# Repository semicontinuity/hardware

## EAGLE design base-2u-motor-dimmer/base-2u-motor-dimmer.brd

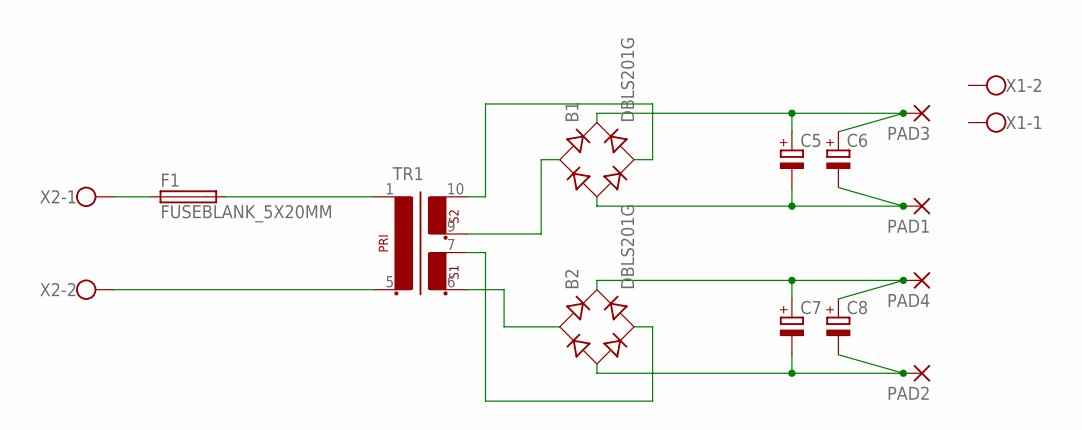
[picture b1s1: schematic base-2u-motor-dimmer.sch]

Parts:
B1, B2: DBLS201G; DBS
C5, C6, C7, C8: CPOL-EUTT2D5L; TT2D5L
F1: FUSEBLANK_5X20MM; FUSE_HOLDER_5X20MM
PAD1, PAD2, PAD3, PAD4: 1,6/0,8
TR1: EI30-2
X1, X2: W237-102

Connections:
unnamed: B2.AC2, TR1.7 (4)
unnamed: B2.AC1, TR1.6 (3)
unnamed: F1.1, X2.1
unnamed: B1.AC1, TR1.9 (5)
unnamed: B1.AC2, TR1.10 (6)
unnamed: B1.+, C5.+, C6.+, PAD3.1
unnamed: B1.-, C5.-, C6.-, PAD1.1
unnamed: B2.-, C7.-, C8.-, PAD2.1
unnamed: B2.+, C7.+, C8.+, PAD4.1

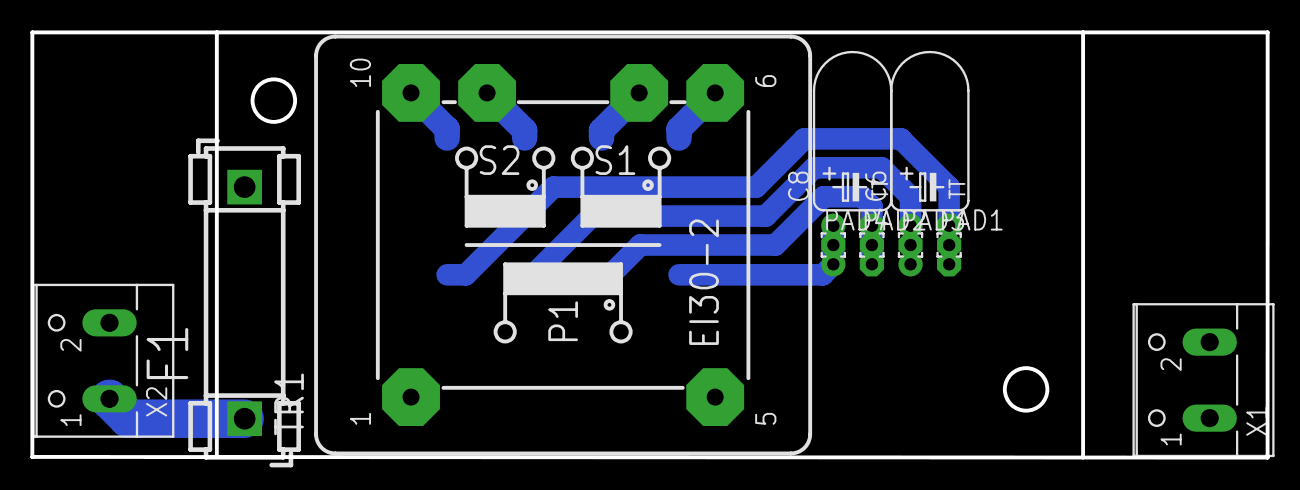
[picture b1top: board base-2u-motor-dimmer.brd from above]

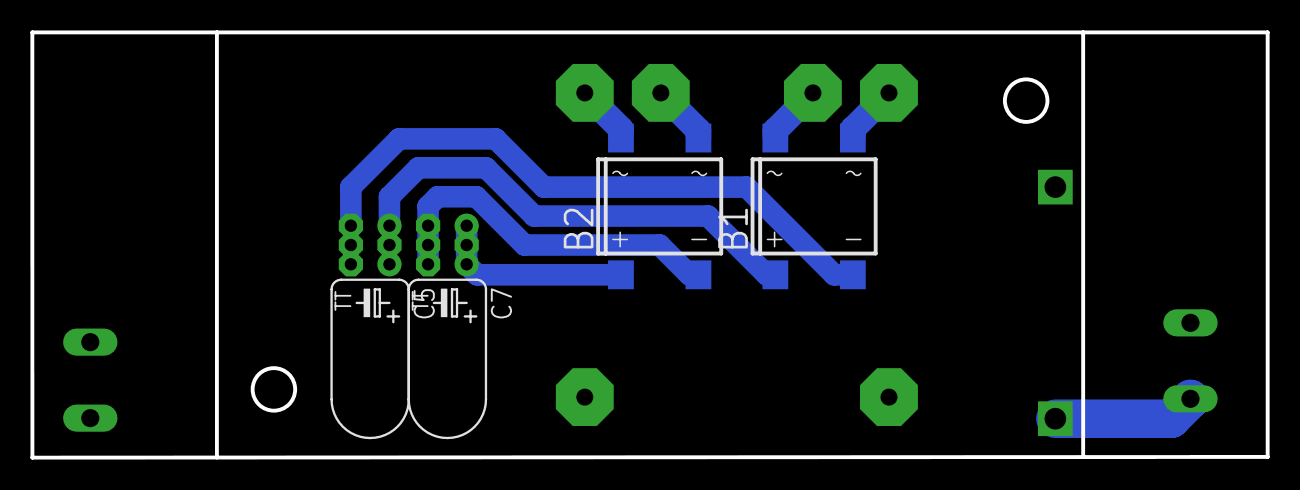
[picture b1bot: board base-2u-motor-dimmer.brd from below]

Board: 2 copper layers, 81.3 x 28.0 mm, 14 parts (4 on the bottom side), 9 nets.

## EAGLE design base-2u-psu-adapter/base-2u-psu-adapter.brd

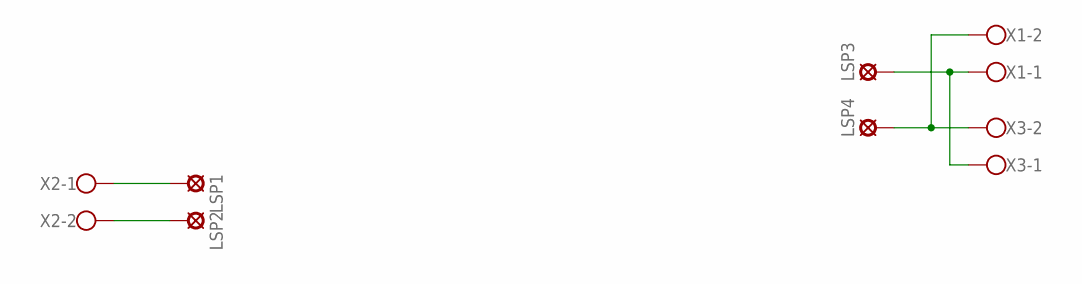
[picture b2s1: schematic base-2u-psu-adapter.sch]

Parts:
LSP1, LSP2, LSP3, LSP4: LSP10
X1, X2, X3: W237-102

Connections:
GND: LSP4.MP, X1.2, X3.2
N: LSP2.MP, X2.2
unnamed: LSP3.MP, X1.1, X3.1
unnamed: LSP1.MP, X2.1

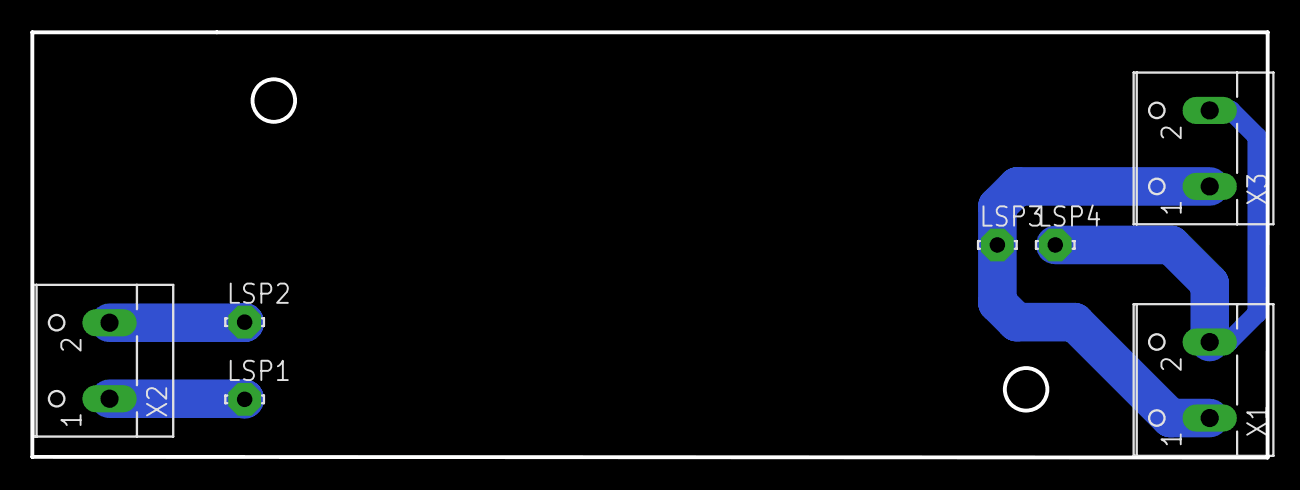
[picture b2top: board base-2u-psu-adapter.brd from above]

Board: 2 copper layers, 81.3 x 28.0 mm, 7 parts (0 on the bottom side), 4 nets.
